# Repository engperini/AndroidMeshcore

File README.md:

# MeshCommunity

**English** · [Português](#português)

**One USB LoRa radio + your Android phone = a MeshCore node, a Meshtastic node or a raw LoRa terminal.
Switch networks with one tap. No firmware flashing, no Bluetooth, no second app.**

<p align="center">

  <br><sub>The same radio running <b>MeshCore</b>, <b>Meshtastic</b> and <b>generic LoRa</b>, one at a time.</sub>
</p>

> [!WARNING]
> Use at your own risk. You are responsible for transmitting only on frequencies and power levels that are legal
> where you are.

## Contents

- [What makes it different: the firmware runs on the phone](#what-makes-it-different-the-firmware-runs-on-the-phone)
- [Supported hardware](#supported-hardware)
- [Quick start](#quick-start)
- [Screens](#screens)
- [Features](#features)
- [Future: the radio without the cable](#future-the-radio-without-the-cable)
- [How it works inside](#how-it-works-inside)
- [Build](#build) · [Tests](#tests) · [Layout](#layout) · [Credits and license](#credits-and-license)

## What makes it different: the firmware runs on the phone

On a normal mesh radio, a microcontroller board runs the firmware and the phone is only a screen, connected over
Bluetooth. The network is decided by the firmware you flash: to go from MeshCore to Meshtastic you take a computer,
flash the board again, and switch to another app.

MeshCommunity turns that around. **The firmware runs inside the app, on the phone.** The USB radio is only a radio
(an SX1262 LoRa chip plus a tiny USB-to-SPI bridge), so it never needs to know which network you use.

```
  The usual way                                    MeshCommunity
  ─────────────                                    ─────────────
  📱 app ──Bluetooth──▶ 📟 board with MCU          📱 app + firmware (MeshCore, Meshtastic, LoRa)
                         └ runs ONE firmware          │
                           (reflash to change)        └──USB OTG──▶ 📻 radio only (no firmware)
```

What this gives you:

| | Usual mesh radio | MeshCommunity |
|---|---|---|
| Change network (MeshCore ↔ Meshtastic) | flash another firmware with a computer | **tap Settings → Mode** |
| Update the firmware | flash the board | **update the app** (APK) |
| Apps | one app per network | **one app** for all |
| Your data when you switch | lost when you reflash | **each mode keeps its own** identity, contacts, channels and messages |
| Radio hardware | board with a microcontroller | a **USB radio with no microcontroller** is enough |
| Link phone ↔ radio | Bluetooth (pairing, range) | **USB cable** (OTG) |
| Clock, GPS, battery | board's own | the **phone's** |

What to keep in mind:

- **One network at a time.** Switching takes a second, but the radio listens to one protocol at a time.
- **The node lives in the phone.** If you unplug the radio or the app is stopped, the node is offline: this is a
  companion for you to carry, not a standalone repeater on a rooftop.
- The radio draws its power from the phone (a few tens of mA receiving).

## Supported hardware

| Radio | What it is | Status |
|---|---|---|
| **USB MeshStick** (e.g. Elecrow MeshStick) | CH341A USB bridge (`1a86:5512`) + SX1262. Plug and play. | ✅ supported, field-tested |
| **Seeed XIAO nRF52840 + Wio-SX1262 kit** | The XIAO only works as a USB-to-SPI bridge, like the MeshStick's CH341: flash the [xiao-sx1262-usb-bridge](https://github.com/engperini/xiao-sx1262-usb-bridge) firmware **once** and never again. | ✅ supported, field-tested |
| **USB LoRa stick, no MCU** (CH341F + Wio-SX1262) | Our own 20.5 × 14 mm board, in [`hardware/`](hardware/), with JLCPCB order files and a 3D-printed case. | 🧪 v0.2 design, not built yet |

All of them run all three modes: the app drives every radio through the same USB driver. The XIAO kit is the
practical choice if you already have one; the MeshStick needs nothing at all.

<p align="center">
  <br>
  <sub>An Android phone + a USB MeshStick on an OTG adapter, receiving the MeshCore Brasil mesh.</sub>
</p>

You also need:

- An Android **8.0+** phone with **USB host/OTG** (almost every current phone).
- An **OTG** adapter or cable (e.g. USB-C → USB-A female).
- An **antenna** on the radio **before** you plug it in.

## Quick start

1. Download **`MeshCommunity.apk`** from [Releases](https://github.com/engperini/AndroidMeshcore/releases/latest) and
   install it (Android asks you to allow installs from unknown sources).
2. Attach the antenna, plug the radio into the phone with OTG, and allow **MeshCommunity to open** and to **access
   the USB device** (tick "always"). The app opens by itself next time you plug it in.
3. Choose the network in **Settings → Mode**, then:

**MeshCore**
- Settings → **LoRa radio**: pick your **region** (Brazil is preset: 923.125 MHz, 62.5 kHz, SF8, CR8), the **path
  bytes** (MeshCore Brasil: 2) and tap **Apply**. Under **Identity**, name your node.
- Menu ⋮ → **Send advert (flood)** so others find you, then say hi in the *Public* channel 👋

**Meshtastic**
- Settings → **Meshtastic radio**: choose the **region** (Meshtastic does not transmit until it is set; in Brazil
  most communities use **ANZ**, LongFast at 919.875 MHz) and keep the **LongFast** preset to talk to the default mesh.
- Under **Meshtastic node**, set your long and short name. Menu ⋮ → **Announce node** so others see you now.
- Chat in **#LongFast**, see who is around in **Nodes**, run a **Traceroute**, and find nodes on the **Map**.

**Generic LoRa**
- Settings → **Generic LoRa radio**: pick a preset or set frequency, bandwidth, SF, CR, sync word and power.
- The **LoRa** tab shows every packet heard on those parameters (text or hex, with RSSI/SNR) and sends your own:
  handy for your own sensors and telemetry.

To update, install the new APK over the old one: every mode keeps its data. Before changing phones, export your
MeshCore key in **Settings → Identity backup**.

> [!TIP]
> Some phones switch OTG off after a while or save battery aggressively. If the radio stops with the screen off,
> turn off battery optimisation for MeshCommunity.

## Screens

The screens are rendered by the app's tests (`ScreenshotTest`) with sample data, in English and Portuguese.

**MeshCore**

**Meshtastic**

**Generic LoRa**

## Features

The app is in **English and Portuguese** (it follows the phone; switch in **Settings → Language**). In every mode
the radio keeps running with the screen off, new messages raise a notification, and the app opens when you plug the
radio in.

### MeshCore mode

The [MeshCore](https://github.com/meshcore-dev/MeshCore) companion firmware (`MyMesh`), the same as on a MeshCore
radio, talking to the app with the official companion protocol.

- 💬 **Chats**: group channels and direct messages in one list, with unread counts.
  - **Channels**: *Public* comes preconfigured. Create a **#hashtag** channel (everyone using the same `#name` joins
    the same chat), a **new private** channel (random key) or join one **with a key**. Long-press → **QR code** to
    share. Your channel messages show **how many repeaters were heard repeating them** (tap to see which).
  - **Direct messages**: *sending → sent → delivered ✓✓* with the round-trip time; tap an unconfirmed one to resend.
  - **Rooms (room servers)**: log in from the chat; posts show their author.
- 👥 **Contacts**: search, filters, sorting and "last seen". Each contact shows its route, with **Discover route**,
  **Ping** for repeaters (SNR at each hop), **Use this route**, **Reset**, **QR code** and zero-hop share.
- 🛠️ **Remote admin** of repeaters, rooms and sensors: login, **status** (battery, uptime, queue, packets, airtime,
  RSSI/SNR, noise) and an encrypted **CLI terminal**. Every request shows *waiting → answered in N s* or *no answer*.
- 🔳 **`meshcore://` QR codes** and links, compatible with the official app.
- 🗺️ **Map** of contacts with GPS (OpenStreetMap, no API key).
- 📊 **Network**: node stats, SNR/RSSI chart, packets by type, **radio diagnostics** and the packet log.
- ⚙️ **Settings**: radio in 3 steps (**region → path bytes → power**, with an *Advanced* section), manual and
  automatic **adverts**, contact rules, telemetry sharing, location, and **identity backup** (export/restore the key).

### Meshtastic mode

The [Meshtastic firmware](https://github.com/meshtastic/firmware) itself (2.8), built for Android. It talks on the
air with any Meshtastic device: T-Beams, Heltecs, RAKs, other phones…

- 💬 **Chats**: the node's channels (the primary shows its preset name, e.g. *LongFast*) and direct messages. Your
  messages show when a node was heard passing them on (implicit ACK); direct ones turn *delivered ✓✓*.
- 📡 **Nodes**: every node heard, with hops, SNR, battery and last heard. **Traceroute** shows the path out and back
  with the SNR of each hop. Menu ⋮ → **Announce node** sends your NodeInfo now.
- 🗺️ **Map**: nodes that share a position. **Share my position** sends the phone's GPS as your node's position.
- ⚙️ **Settings**: long and short name, **region**, modem preset, hop limit, power, and **channels** (name and key,
  add or delete).
- The node uses the phone's clock and GPS, and runs in its own Android process.

### Generic LoRa mode

Raw LoRa packets with free parameters: frequency, bandwidth 7.8–500 kHz, SF5–12, CR 4/5–4/8, sync word, preamble and
power. Every packet heard shows up as **text or hex** with **RSSI/SNR** and a signal chart, and you can send your
own. Presets listen to the MeshCore and Meshtastic channels. Good for your own sensors, telemetry and experiments.

### MeshCore mode compared

| Feature | Official MeshCore app | MeshCoreRPI (Pi) | MeshCommunity |
|---|---|---|---|
| How it reaches the radio | BLE/USB to a node running firmware | SPI/USB on the Pi; clients over TCP | **USB OTG to the radio, the node runs on the phone** |
| Public, #hashtag and private channels | ✅ | via a client | ✅ |
| Direct messages with ACK and resend | ✅ | via a client | ✅ |
| Rooms (room servers) | ✅ | via a client | ✅ |
| Repeater admin (login, status, CLI) | ✅ | ✅ | ✅ |
| Discover / set route, ping with SNR per hop | ✅ | — | ✅ |
| `meshcore://` QR codes | ✅ | — | ✅ |
| Map | ✅ | ✅ (web) | ✅ |
| Stats, charts, packet log, radio diagnostics | partial | ✅ (web) | ✅ |
| Identity backup | ✅ | — | ✅ |
| Also runs Meshtastic and generic LoRa | — | — | ✅ |
| Sensor telemetry | ✅ | — | not yet |

## Future: the radio without the cable

Today the radio is plugged into the phone. These are the next ideas, keeping what makes MeshCommunity different:
**the protocols run in the app, and the radio never needs to be flashed to change networks.**

**1. A LoRa modem over Bluetooth or Wi-Fi.** Over USB the phone drives the radio chip command by command, which
needs the ~0.3 ms round trips of a cable. Without a cable the radio needs a small microcontroller that speaks in
whole packets: *"set 919.875 MHz, SF11"*, *"send these 40 bytes"*, *"received 52 bytes, RSSI −97"*. That is one
message per packet, fine over Bluetooth or Wi-Fi.

A modem is not the same as the official firmware, even on the same board:

| | Official firmware | LoRa modem |
|---|---|---|
| Knows | the whole protocol: routing, encryption, channels, nodes | only the radio: bytes in, bytes out |
| Networks | one, the one flashed | any; it doesn't know which |
| Change network or update the protocol | flash the board | tap in the app / update the app |
| Without the phone | keeps relaying and storing messages | does nothing |

So for one network and a wireless radio, the official firmware on a Bluetooth board is the simpler choice; the
modem is for using several networks, raw LoRa, or new protocols with one radio. The idea is proven: ham radio's KISS
TNCs (APRSdroid over Bluetooth) and Reticulum's [RNode](https://github.com/markqvist/RNode_Firmware) are LoRa
modems of this kind. Speaking the RNode protocol, if it fits, would let boards already flashed with RNode work here.

**2. The Raspberry Pi as the home radio.** Many of us already keep a Pi with an SX1262 and the antenna at the window,
running a MeshCore repeater (e.g. with [MeshCoreRPI](https://github.com/engperini/MeshCoreRPI)). The Pi would run a
small radio server, and the app would connect to it over the home Wi-Fi: from the sofa, switch the window antenna to
Meshtastic to see the community chat, use the generic LoRa terminal, or back to MeshCore. When the phone lets go,
the Pi goes back to being the repeater. (One radio listens on one frequency at a time: while you use Meshtastic,
the MeshCore repeater pauses.)

**3. MeshCore repeater and companion on the same radio.** The MeshCore companion firmware only lets a companion
repeat on 433.000, 869.000 and 918.000 MHz, so not on the Brazilian 923.125 MHz. That is a deliberate network rule.
Instead of bypassing it, the same radio can carry two nodes side by side: a real **repeater**, with its own identity
and announced as a repeater, and **your companion**. The Pi at the window, or the USB radio on the phone, serves
both.

## How it works inside

```
┌─────────────────────────── Android phone ───────────────────────────┐
│  MeshCommunity UI (Compose): chats, contacts/nodes, map, settings     │
│        │                                   │                          │
│  libmeshcore.so (NDK)                  :meshtastic process            │
│   ├ MeshCore companion firmware        libmeshtastic.so (NDK)         │
│   └ generic LoRa mode                   └ Meshtastic firmware 2.8      │
│        │                                   │                          │
│        └──────── USB radio driver (usbdevfs, no root) ────────┘        │
└──────────────────────────────────┬──────────────────────────────────┘
                                   │ USB OTG
        MeshStick (CH341 + SX1262) · XIAO + Wio-SX1262 bridge · USB LoRa stick
```

- **MeshCore** runs in `libmeshcore.so`, ported from [MeshCoreRPI](https://github.com/engperini/MeshCoreRPI).
  The generic LoRa mode lives in the same library.
- **Meshtastic** runs in `libmeshtastic.so`: the firmware's portduino/WASM build compiled for Android, in its own
  process, so a node restart is simply a fresh process.
- Both drive the SX1262 through the same USB code, over Android's USB host API (no root).
- Each protocol keeps its own data in the app: identities, nodes, channels, and the message history in SQLite.

## Build

Requirements: JDK 17, Android SDK (platform 35), NDK `27.2.12479018` and CMake `3.22.1`.

```bash
./gradlew assembleDebug        # app/build/outputs/apk/debug/app-debug.apk
./gradlew assembleRelease      # R8-minified APK
```

Every build, local or CI, is signed with the public test key in `app/meshcore-debug.jks`, so new APKs install over
the previous one and keep your data. It is public on purpose: anyone can build and contribute. A fork can use its own
key with `MESHCORE_KEYSTORE_FILE`, `MESHCORE_KEYSTORE_PASSWORD`, `MESHCORE_KEY_ALIAS` and `MESHCORE_KEY_PASSWORD`.

## Tests

- `tools/hosttest` builds a **MeshCore PC node** from the same sources as `libmeshcore.so`, with a UDP "radio".
  `TwoNodeMeshTest` runs two of them and drives them with the app's protocol code: adverts, direct messages with
  ACK, channels, routes, links, key backup and more.
- `tools/meshtastic/hosttest` builds the **Meshtastic engine on the PC** with the same sources and glue as the app
  (simulated radio) and drives it like the app does: config, rename, text, traceroute, region, position.
- `ScreenshotTest` / `ScreenshotTestEn` (Robolectric) render the screens above.

```bash
tools/hosttest/build.sh
tools/meshtastic/hosttest/build.sh
./gradlew testDebugUnitTest
```

GitHub Actions runs all of them and builds the APK on every push; a manual run with a version publishes the release.

## Layout

| Path | What it is |
|---|---|
| `app/src/main/cpp/meshcore/` | MeshCore core and companion firmware, ed25519 and Crypto, from MeshCoreRPI |
| `app/src/main/cpp/android/` | USB radio buses (`Ch341Bridge`, `XiaoBridge`), SX1262 driver, JNI of `libmeshcore.so` |
| `app/src/main/cpp/meshtastic/` | Meshtastic engine: firmware and libraries in `vendor/` (fetched by `tools/meshtastic/vendor.sh` at fixed revisions), Android glue in `android/` |
| `app/src/main/java/.../core/` | Controllers: `MeshController` (MeshCore), `MeshtasticController`, `LoraController` (modes, generic LoRa) |
| `app/src/main/java/.../mt/` | Meshtastic engine process (`MtEngineService`) |
| `app/src/main/java/.../service/` | Foreground service and USB (permission, wake lock, notifications) |
| `app/src/main/java/.../ui/` | Compose screens |
| `hardware/` | No-MCU USB LoRa stick (KiCad, JLCPCB files) and 3D-printed cases |
| `tools/` | PC test nodes for MeshCore and Meshtastic |

## Credits and license

- [MeshCore](https://github.com/meshcore-dev/MeshCore) by Scott Powell / rippleradios.com: MIT.
- [MeshCoreRPI](https://github.com/engperini/MeshCoreRPI): native Linux port, SX1262 and CH341 driver.
- [Meshtastic firmware](https://github.com/meshtastic/firmware) by the Meshtastic developers: **GPL-3.0**, with
  [RadioLib](https://github.com/jgromes/RadioLib) (MIT), [portduino](https://github.com/meshtastic/framework-portduino)
  (GPL-3.0), [nanopb](https://github.com/nanopb/nanopb) (zlib) and the other libraries listed in
  [`app/src/main/cpp/meshtastic/vendor/LICENSES.md`](app/src/main/cpp/meshtastic/vendor/LICENSES.md).
- [Arduino Crypto](https://github.com/rweather/arduinolibs) by Rhys Weatherley: MIT. ed25519 by Orson Peters: zlib.

This repository's own code is under the MIT license, see [LICENSE](LICENSE). The Meshtastic engine is GPL-3.0, so
the **APK, which includes it, is distributed under GPL-3.0**; its complete source is this repository.

If MeshCommunity is useful to you, a ⭐ on GitHub helps other people find it.

---

# Português

[English](#meshcommunity) · **Português**

**Um rádio LoRa USB + seu celular Android = um nó MeshCore, um nó Meshtastic ou um terminal LoRa.
Troque de rede com um toque. Sem gravar firmware, sem Bluetooth, sem segundo app.**

<p align="center">

  <br><sub>O mesmo rádio rodando <b>MeshCore</b>, <b>Meshtastic</b> e <b>LoRa genérico</b>, um de cada vez.</sub>
</p>

> [!WARNING]
> Use por sua conta e risco. Você é responsável por transmitir só em frequências e potências permitidas onde você
> está.

## Índice

- [O diferencial: o firmware roda no celular](#o-diferencial-o-firmware-roda-no-celular)
- [Hardware compatível](#hardware-compatível)
- [Começo rápido](#começo-rápido)
- [Telas](#telas)
- [Funcionalidades](#funcionalidades)
- [Futuro: o rádio sem o cabo](#futuro-o-rádio-sem-o-cabo)
- [Como funciona por dentro](#como-funciona-por-dentro)
- [Compilar](#compilar) · [Testes](#testes) · [Estrutura](#estrutura) · [Créditos e licença](#créditos-e-licença)

## O diferencial: o firmware roda no celular

Num rádio mesh comum, uma placa com microcontrolador roda o firmware e o celular é só a tela, ligado por Bluetooth.
Quem decide a rede é o firmware gravado: para trocar de MeshCore para Meshtastic, você pega um computador, grava a
placa de novo e troca de app.

O MeshCommunity inverte isso. **O firmware roda dentro do app, no celular.** O rádio USB é só rádio (um chip LoRa
SX1262 e uma pequena ponte USB→SPI), então ele nem precisa saber qual rede você usa.

```
  O jeito comum                                    MeshCommunity
  ─────────────                                    ─────────────
  📱 app ──Bluetooth──▶ 📟 placa com MCU           📱 app + firmware (MeshCore, Meshtastic, LoRa)
                         └ roda UM firmware           │
                           (regravar para trocar)     └──USB OTG──▶ 📻 só o rádio (sem firmware)
```

O que você ganha:

| | Rádio mesh comum | MeshCommunity |
|---|---|---|
| Trocar de rede (MeshCore ↔ Meshtastic) | gravar outro firmware com um computador | **tocar em Config → Modo** |
| Atualizar o firmware | gravar a placa | **atualizar o app** (APK) |
| Apps | um app para cada rede | **um app** para todas |
| Seus dados ao trocar | perdidos ao regravar | **cada modo guarda os seus**: identidade, contatos, canais e mensagens |
| Hardware do rádio | placa com microcontrolador | basta um **rádio USB sem microcontrolador** |
| Ligação celular ↔ rádio | Bluetooth (pareamento, alcance) | **cabo USB** (OTG) |
| Relógio, GPS, bateria | os da placa | os do **celular** |

O que é bom saber:

- **Uma rede por vez.** A troca leva um segundo, mas o rádio escuta um protocolo de cada vez.
- **O nó mora no celular.** Se você desplugar o rádio ou o app for encerrado, o nó fica fora do ar: é um companheiro
  para levar com você, não um repetidor autônomo no telhado.
- O rádio é alimentado pelo celular (algumas dezenas de mA recebendo).

## Hardware compatível

| Rádio | O que é | Status |
|---|---|---|
| **USB MeshStick** (ex.: Elecrow MeshStick) | Ponte USB CH341A (`1a86:5512`) + SX1262. Plugar e usar. | ✅ suportado, testado em campo |
| **Kit Seeed XIAO nRF52840 + Wio-SX1262** | O XIAO só faz a ponte USB→SPI, como o CH341 do MeshStick: grave o firmware [xiao-sx1262-usb-bridge](https://github.com/engperini/xiao-sx1262-usb-bridge) **uma vez** e nunca mais. | ✅ suportado, testado em campo |
| **Pendrive LoRa sem MCU** (CH341F + Wio-SX1262) | Nossa placa de 20,5 × 14 mm, em [`hardware/`](hardware/), com os arquivos para pedir na JLCPCB e caixinha para impressora 3D. | 🧪 projeto v0.2, ainda não fabricado |

Todos rodam os três modos: o app usa o mesmo driver USB para qualquer rádio. O kit XIAO é a escolha prática para quem
já tem um; o MeshStick não precisa de nada.

<p align="center">
  <br>
  <sub>Celular Android + USB MeshStick num adaptador OTG, recebendo a malha MeshCore Brasil.</sub>
</p>

Você também precisa de:

- Celular Android **8.0** ou mais novo com **USB Host/OTG** (quase todos os atuais).
- Adaptador ou cabo **OTG** (USB-C → USB-A fêmea, por exemplo).
- **Antena** conectada ao rádio **antes** de plugar.

## Começo rápido

1. Baixe o **`MeshCommunity.apk`** em [Releases](https://github.com/engperini/AndroidMeshcore/releases/latest) e
   instale (o Android pede para permitir a instalação de fontes desconhecidas).
2. Coloque a antena, plugue o rádio no celular pelo OTG e aceite **abrir o MeshCommunity** e **permitir o acesso ao
   dispositivo USB** (marque "usar sempre"). Da próxima vez, o app abre sozinho quando você plugar.
3. Escolha a rede em **Config → Modo** e então:

**MeshCore**
- Config → **Rádio LoRa**: escolha a **região** (o Brasil já vem pronto: 923,125 MHz, 62,5 kHz, SF8, CR8), os
  **bytes do caminho** (MeshCore Brasil: 2) e toque em **Aplicar**. Em **Identidade**, dê um nome ao seu nó.
- Menu ⋮ → **Enviar advert (flood)** para ser encontrado e dê um oi no canal *Public* 👋

**Meshtastic**
- Config → **Rádio Meshtastic**: escolha a **região** (o Meshtastic não transmite até ela ser definida; no Brasil a
  maioria das comunidades usa **ANZ**, LongFast em 919,875 MHz) e mantenha o preset **LongFast** para falar com a malha
  padrão.
- Em **Nó Meshtastic**, defina o nome longo e o curto. Menu ⋮ → **Anunciar nó** para aparecer para os outros na hora.
- Converse no **#LongFast**, veja quem está por perto em **Nós**, faça um **Traceroute** e encontre os nós no **Mapa**.

**LoRa genérico**
- Config → **Rádio LoRa genérico**: escolha uma predefinição ou ajuste frequência, largura de banda, SF, CR, sync word
  e potência.
- A aba **LoRa** mostra cada pacote ouvido com esses parâmetros (texto ou hex, com RSSI/SNR) e envia os seus: útil
  para seus sensores e telemetria.

Para atualizar, instale o APK novo por cima: todos os modos mantêm seus dados. Antes de trocar de celular, exporte sua
chave do MeshCore em **Config → Backup da identidade**.

> [!TIP]
> Alguns celulares desligam o OTG depois de um tempo ou economizam bateria de forma agressiva. Se o rádio parar com a
> tela apagada, desative a otimização de bateria para o MeshCommunity.

## Telas

As telas são geradas pelos testes do app (`ScreenshotTest`) com dados de exemplo, em português e inglês.

**MeshCore**

**Meshtastic**

**LoRa genérico**

## Funcionalidades

O app está em **português e inglês** (segue o idioma do celular; troque em **Config → Idioma**). Em todos os modos o
rádio continua ativo com a tela apagada, mensagens novas geram notificação e o app abre quando você pluga o rádio.

### Modo MeshCore

O firmware companion do [MeshCore](https://github.com/meshcore-dev/MeshCore) (`MyMesh`), o mesmo de um rádio
MeshCore, conversando com o app pelo protocolo companion oficial.

- 💬 **Conversas**: canais em grupo e mensagens diretas numa lista só, com não lidas.
  - **Canais**: o *Public* já vem configurado. Crie um canal **#hashtag** (todos que usam o mesmo `#nome` entram na
    mesma conversa), um canal **privado novo** (chave aleatória) ou entre num canal **com chave**. Toque e segure →
    **QR code** para compartilhar. Suas mensagens no canal mostram **quantas repetidoras foram ouvidas repassando**
    (toque para ver quais).
  - **Mensagens diretas**: *enviando → enviado → entregue ✓✓* com o tempo de ida e volta; toque numa sem
    confirmação para reenviar.
  - **Salas (room servers)**: login pelo próprio chat; as mensagens mostram o autor.
- 👥 **Contatos**: busca, filtros, ordenação e "visto há". Cada contato mostra a rota, com **Descobrir rota**,
  **Ping** para repetidores (SNR em cada salto), **Usar esta rota**, **Redefinir**, **QR code** e compartilhar
  zero-hop.
- 🛠️ **Administração remota** de repetidores, salas e sensores: login, **status** (bateria, uptime, fila, pacotes,
  tempo no ar, RSSI/SNR, ruído) e **terminal CLI** criptografado. Cada pedido mostra *aguardando → respondeu em N s*
  ou *sem resposta*.
- 🔳 **QR codes e links `meshcore://`**, compatíveis com o app oficial.
- 🗺️ **Mapa** dos contatos com GPS (OpenStreetMap, sem chave de API).
- 📊 **Rede**: estatísticas do nó, gráfico de SNR/RSSI, pacotes por tipo, **diagnóstico do rádio** e log de pacotes.
- ⚙️ **Config**: rádio em 3 passos (**região → bytes do caminho → potência**, com seção *Avançado*), **advert**
  manual e automático, regras de contatos, compartilhamento de telemetria, localização e **backup da identidade**
  (exportar/restaurar a chave).

### Modo Meshtastic

O próprio [firmware Meshtastic](https://github.com/meshtastic/firmware) (2.8), compilado para Android. Ele conversa
no ar com qualquer aparelho Meshtastic: T-Beam, Heltec, RAK, outros celulares…

- 💬 **Conversas**: os canais do nó (o primário mostra o nome do preset, ex.: *LongFast*) e mensagens diretas. Suas
  mensagens mostram quando um nó foi ouvido repassando (ACK implícito); as diretas ficam *entregue ✓✓*.
- 📡 **Nós**: todos os nós ouvidos, com saltos, SNR, bateria e quando foi ouvido. O **Traceroute** mostra o caminho de
  ida e volta com o SNR de cada salto. Menu ⋮ → **Anunciar nó** envia seu NodeInfo na hora.
- 🗺️ **Mapa**: os nós que compartilham posição. **Compartilhar posição** envia o GPS do celular como a posição do
  seu nó.
- ⚙️ **Config**: nome longo e curto, **região**, preset do modem, limite de saltos, potência e **canais** (nome e
  chave, adicionar ou excluir).
- O nó usa o relógio e o GPS do celular e roda num processo Android próprio.

### Modo LoRa genérico

Pacotes LoRa crus com parâmetros livres: frequência, largura de banda de 7,8 a 500 kHz, SF5–12, CR 4/5–4/8, sync word,
preâmbulo e potência. Cada pacote ouvido aparece em **texto ou hex** com **RSSI/SNR** e gráfico de sinal, e você pode
enviar os seus. Há predefinições para ouvir os canais MeshCore e Meshtastic. Bom para seus sensores, telemetria e
experiências.

### Comparação do modo MeshCore

| Funcionalidade | App oficial MeshCore | MeshCoreRPI (Pi) | MeshCommunity |
|---|---|---|---|
| Como chega ao rádio | BLE/USB com um nó que roda firmware | SPI/USB no Pi; clientes por TCP | **USB OTG no rádio, o nó roda no celular** |
| Canais Public, #hashtag e privados | ✅ | via cliente | ✅ |
| Mensagens diretas com ACK e reenvio | ✅ | via cliente | ✅ |
| Salas (room servers) | ✅ | via cliente | ✅ |
| Admin de repetidor (login, status, CLI) | ✅ | ✅ | ✅ |
| Descobrir/definir rota, ping com SNR por salto | ✅ | — | ✅ |
| QR codes `meshcore://` | ✅ | — | ✅ |
| Mapa | ✅ | ✅ (web) | ✅ |
| Estatísticas, gráficos, log de pacotes, diagnóstico do rádio | parcial | ✅ (web) | ✅ |
| Backup da identidade | ✅ | — | ✅ |
| Também roda Meshtastic e LoRa genérico | — | — | ✅ |
| Telemetria de sensores | ✅ | — | ainda não |

## Futuro: o rádio sem o cabo

Hoje o rádio fica plugado no celular. Estas são as próximas ideias, mantendo o que faz o MeshCommunity diferente:
**os protocolos rodam no app, e o rádio nunca precisa ser regravado para trocar de rede.**

**1. Um modem LoRa por Bluetooth ou Wi-Fi.** Pela USB, o celular controla o chip do rádio comando por comando, o que
exige as idas e voltas de ~0,3 ms de um cabo. Sem cabo, o rádio precisa de um pequeno microcontrolador que fala em
pacotes inteiros: *"ajuste 919,875 MHz, SF11"*, *"transmita estes 40 bytes"*, *"recebi 52 bytes, RSSI −97"*. É uma
mensagem por pacote, o que funciona bem por Bluetooth ou Wi-Fi.

Um modem não é o mesmo que o firmware oficial, mesmo na mesma placa:

| | Firmware oficial | Modem LoRa |
|---|---|---|
| Sabe | o protocolo inteiro: roteamento, criptografia, canais, nós | só o rádio: bytes entram, bytes saem |
| Redes | uma, a que foi gravada | qualquer uma; ele nem sabe qual |
| Trocar de rede ou atualizar o protocolo | regravar a placa | um toque no app / atualizar o app |
| Sem o celular | continua repetindo e guardando mensagens | não faz nada |

Por isso, para uma rede só com rádio sem fio, o firmware oficial numa placa com Bluetooth é a escolha mais simples; o
modem é para usar várias redes, LoRa livre ou protocolos novos com um rádio só. A ideia é comprovada: os TNC KISS do
radioamador (o APRSdroid usa por Bluetooth) e o [RNode](https://github.com/markqvist/RNode_Firmware) da rede
Reticulum são modems LoRa desse tipo. Falar o protocolo do RNode, se ele servir, permitiria usar aqui placas que já
têm o firmware RNode.

**2. O Raspberry Pi como o rádio de casa.** Muita gente já deixa um Pi com SX1262 e a antena na janela, rodando um
repetidor MeshCore (por exemplo com o [MeshCoreRPI](https://github.com/engperini/MeshCoreRPI)). O Pi rodaria um pequeno
servidor de rádio, e o app se conectaria a ele pelo Wi-Fi de casa: do sofá, você troca a antena da janela para o
Meshtastic e vê a conversa da comunidade, usa o terminal LoRa genérico ou volta para o MeshCore. Quando o celular
solta, o Pi volta a ser o repetidor. (Um rádio escuta uma frequência por vez: enquanto você usa o Meshtastic, o
repetidor MeshCore pausa.)

**3. Repetidor e companion MeshCore no mesmo rádio.** O firmware companion do MeshCore só deixa um companion repetir
em 433,000, 869,000 e 918,000 MHz, ou seja, não nos 923,125 MHz do Brasil. É uma regra intencional da rede. Em vez de
furá-la, o mesmo rádio pode carregar dois nós lado a lado: um **repetidor de verdade**, com identidade própria e
anunciado como repetidor, e o **seu companion**. O Pi na janela, ou o rádio USB no celular, atende os dois.

## Como funciona por dentro

```
┌────────────────────────── celular Android ──────────────────────────┐
│  Interface do MeshCommunity (Compose): conversas, contatos/nós, mapa  │
│        │                                   │                          │
│  libmeshcore.so (NDK)                  processo :meshtastic           │
│   ├ firmware companion MeshCore        libmeshtastic.so (NDK)         │
│   └ modo LoRa genérico                  └ firmware Meshtastic 2.8      │
│        │                                   │                          │
│        └────── driver USB do rádio (usbdevfs, sem root) ──────┘        │
└──────────────────────────────────┬──────────────────────────────────┘
                                   │ USB OTG
        MeshStick (CH341 + SX1262) · ponte XIAO + Wio-SX1262 · pendrive LoRa
```

- O **MeshCore** roda na `libmeshcore.so`, portada do [MeshCoreRPI](https://github.com/engperini/MeshCoreRPI). O modo
  LoRa genérico fica na mesma biblioteca.
- O **Meshtastic** roda na `libmeshtastic.so`: a versão portduino/WASM do firmware compilada para Android, num
  processo próprio, então reiniciar o nó é só iniciar um processo novo.
- Os dois controlam o SX1262 pelo mesmo código USB, pela API de USB host do Android (sem root).
- Cada protocolo guarda seus dados no app: identidades, nós, canais e o histórico de mensagens em SQLite.

## Compilar

Requisitos: JDK 17, Android SDK (platform 35), NDK `27.2.12479018` e CMake `3.22.1`.

```bash
./gradlew assembleDebug        # app/build/outputs/apk/debug/app-debug.apk
./gradlew assembleRelease      # APK com R8
```

Todo build, local ou no CI, é assinado com a chave pública de teste em `app/meshcore-debug.jks`, então os APKs novos
instalam por cima e mantêm seus dados. Ela é pública de propósito, para qualquer pessoa compilar e contribuir. Um fork
pode usar a própria chave com `MESHCORE_KEYSTORE_FILE`, `MESHCORE_KEYSTORE_PASSWORD`, `MESHCORE_KEY_ALIAS` e
`MESHCORE_KEY_PASSWORD`.

## Testes

- `tools/hosttest` gera um **nó MeshCore para PC** com as mesmas fontes da `libmeshcore.so`, com um "rádio" UDP. O
  `TwoNodeMeshTest` roda dois deles e os controla com o código de protocolo do app: adverts, mensagens diretas com
  ACK, canais, rotas, links, backup da chave e mais.
- `tools/meshtastic/hosttest` gera o **motor Meshtastic no PC** com as mesmas fontes e cola do app (rádio simulado) e
  o controla como o app: configuração, nome, texto, traceroute, região e posição.
- `ScreenshotTest` / `ScreenshotTestEn` (Robolectric) geram as telas acima.

```bash
tools/hosttest/build.sh
tools/meshtastic/hosttest/build.sh
./gradlew testDebugUnitTest
```

O GitHub Actions roda todos eles e gera o APK a cada push; uma execução manual com a versão publica a release.

## Estrutura

| Caminho | O que é |
|---|---|
| `app/src/main/cpp/meshcore/` | Núcleo e firmware companion do MeshCore, ed25519 e Crypto, do MeshCoreRPI |
| `app/src/main/cpp/android/` | Barramentos USB do rádio (`Ch341Bridge`, `XiaoBridge`), driver SX1262, JNI da `libmeshcore.so` |
| `app/src/main/cpp/meshtastic/` | Motor Meshtastic: firmware e bibliotecas em `vendor/` (baixados por `tools/meshtastic/vendor.sh` em revisões fixas), cola Android em `android/` |
| `app/src/main/java/.../core/` | Controladores: `MeshController` (MeshCore), `MeshtasticController`, `LoraController` (modos, LoRa genérico) |
| `app/src/main/java/.../mt/` | Processo do motor Meshtastic (`MtEngineService`) |
| `app/src/main/java/.../service/` | Serviço em primeiro plano e USB (permissão, wake lock, notificações) |
| `app/src/main/java/.../ui/` | Telas Compose |
| `hardware/` | Pendrive LoRa USB sem MCU (KiCad, arquivos JLCPCB) e caixinhas para impressão 3D |
| `tools/` | Nós de teste para PC, MeshCore e Meshtastic |

## Créditos e licença

- [MeshCore](https://github.com/meshcore-dev/MeshCore), de Scott Powell / rippleradios.com: MIT.
- [MeshCoreRPI](https://github.com/engperini/MeshCoreRPI): port nativo para Linux, driver SX1262 e CH341.
- [Firmware Meshtastic](https://github.com/meshtastic/firmware), dos desenvolvedores do Meshtastic: **GPL-3.0**, com
  [RadioLib](https://github.com/jgromes/RadioLib) (MIT), [portduino](https://github.com/meshtastic/framework-portduino)
  (GPL-3.0), [nanopb](https://github.com/nanopb/nanopb) (zlib) e as outras bibliotecas listadas em
  [`app/src/main/cpp/meshtastic/vendor/LICENSES.md`](app/src/main/cpp/meshtastic/vendor/LICENSES.md).
- [Arduino Crypto](https://github.com/rweather/arduinolibs), de Rhys Weatherley: MIT. ed25519, de Orson Peters: zlib.

O código próprio deste repositório está sob a licença MIT, veja [LICENSE](LICENSE). O motor Meshtastic é GPL-3.0, por
isso o **APK, que o inclui, é distribuído sob a GPL-3.0**; o código-fonte completo é este repositório.

Se o MeshCommunity for útil para você, uma ⭐ no GitHub ajuda outras pessoas a encontrá-lo.

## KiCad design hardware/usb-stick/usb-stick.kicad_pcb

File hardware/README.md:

# Hardware

**English** · [Português](#português)

Two ways to give the phone a LoRa radio over USB, both running the MeshCore node **on the phone**:

| | USB LoRa stick (this folder) | XIAO kit |
|---|---|---|
| Inside | CH341F + Seeed Wio-SX1262 module | Seeed XIAO nRF52840 + Wio-SX1262 |
| Microcontroller | **none** | nRF52840, as a USB-SPI bridge |
| Firmware to flash | **none** | [xiao-sx1262-usb-bridge](https://github.com/engperini/xiao-sx1262-usb-bridge) |
| Works with | this app | this app (bridge firmware) or the official MeshCore app (MeshCore firmware) |
| Size | board 20.5 × 14 mm | 21 × 17.8 mm stack |
| Status | **v0.2 design, not built yet** | tested |

Both use the same case design: a straight USB-C male-male adapter inside a small 3D-printed box.

## USB LoRa stick (`usb-stick/`)

Same wiring as the USB MeshStick, so the app's CH341 driver works unchanged:

| CH341F | SX1262 module |
|---|---|
| D0 | NSS |
| D2 | RESET |
| D4 | BUSY |
| D6 | DIO1 |
| D3 / D5 / D7 | SCK / MOSI / MISO |
| D1 | RF_SW (high = receive) |

- The **Wio-SX1262** is the same radio as in the XIAO kit: 11.6 × 11 mm, TCXO on DIO3, DIO2 switches it to
  transmit internally, IPEX for the antenna. Its RF_SW pin selects receive; the app drives it from CH341 D1,
  the pin the MeshStick leaves free for RXEN (on a MeshStick D1 is unconnected, so nothing changes there).
- The CH341F runs on its **internal clock** (no crystal) and starts in SPI mode, `1a86:5512`,
  because SDA is tied low.
- 3.3 V from an ME6211 LDO (500 mA).
- Green LED: on when the phone has configured the stick.
- Board: 20.5 × 14 mm, 2 layers, 1.6 mm. Everything is on top except the radio module, which is
  **hand-soldered on the back** (12 edge pads, 1.27 mm pitch). The antenna plugs into the module's IPEX.

### Ordering at JLCPCB

1. **PCB:** upload `usb-stick/fab/usb-stick-gerbers.zip` (2 layers, 1.6 mm, any colour).
2. **Assembly (top side):** upload `usb-stick-bom.csv` and `usb-stick-cpl.csv`. In the placement preview,
   check the rotation of U1 (pin 1 dot), U2, U3, D1 and J1, and fix any that JLCPCB shows turned.
3. **By hand:** buy the Seeed **Wio-SX1262** module (the HF one, 862–930 MHz, with IPEX) and solder it on the
   back: pin 1 (RF_SW) at the mark, IPEX towards the far end (the silkscreen shows both). A fine tip and flux
   are enough for the 1.27 mm edge pads.
4. Connect the antenna, plug the stick into the phone through the straight USB-C male-male adapter, open the
   app.

### Rebuilding

The board is generated from code: `gen_board.py` (parts and netlist), `route.py` (a small two-layer
negotiated router), `drc.py` (KiCad DRC) and `fab.py` (JLCPCB files). `build.sh` runs them all. You can also
open `usb-stick.kicad_pcb` in KiCad 7+ and edit it by hand.

### Known limits of v0.1

- It uses a **female** USB-C socket plus the adapter, because JLCPCB's parts library has no board-mount
  male plug. A male plug would make it shorter.
- The Wio-SX1262 is not in JLCPCB's library, so it is soldered by hand.
- The land pattern comes from Seeed's own footprint file; check pin 1 and the IPEX corner against the module.
- Needs the app version that drives D1 as RXEN (after v0.2.0).
- Not built or tested yet. Treat v0.2 as a prototype. (v0.1, with a Waveshare Core1262-HF, is in the git
  history.)

## Cases (`cases/`)

OpenSCAD sources with the measurements at the top, and ready STL files:

| File | For |
|---|---|
| `case_stick_base.stl`, `case_stick_lid.stl` | the USB LoRa stick |
| `case_xiao_base.stl`, `case_xiao_lid.stl` | the XIAO nRF52840 + Wio-SX1262 kit |

- Import the STL files in Bambu Studio (or any slicer). PLA or PETG, 0.2 mm layers, no supports: print the
  base open side up and the lid flat side down.
- **Measure your adapter and boards first.** Straight USB-C adapters vary; the defaults are typical sizes.
  Change the numbers at the top of `case_*.scad`, then export again in OpenSCAD (F6, then *Export as STL*), or
  run `openscad -o case_stick_base.stl -D 'part="base"' case_stick.scad`.
- The adapter sits behind a thin front lip, so it does not come out when you unplug from the phone. The lid
  is a press fit (`fit` in `case_lib.scad`). The rear slot is for the antenna cable.

---

## Português

Duas formas de dar ao celular um rádio LoRa pela USB, as duas com o nó MeshCore rodando **no celular**:

| | Pendrive LoRa (esta pasta) | Kit XIAO |
|---|---|---|
| Dentro | CH341F + módulo Seeed Wio-SX1262 | Seeed XIAO nRF52840 + Wio-SX1262 |
| Microcontrolador | **nenhum** | nRF52840, como ponte USB-SPI |
| Firmware para gravar | **nenhum** | [xiao-sx1262-usb-bridge](https://github.com/engperini/xiao-sx1262-usb-bridge) |
| Funciona com | este app | este app (firmware da ponte) ou o app oficial do MeshCore (firmware MeshCore) |
| Tamanho | placa de 20,5 × 14 mm | conjunto de 21 × 17,8 mm |
| Situação | **projeto v0.2, ainda não fabricado** | testado |

As duas usam a mesma ideia de caixinha: um adaptador USB-C macho-macho reto dentro de uma caixa impressa em 3D.

## Pendrive LoRa (`usb-stick/`)

Mesma ligação do USB MeshStick, então o driver do CH341 no app funciona sem mudança:

| CH341F | Módulo SX1262 |
|---|---|
| D0 | NSS |
| D2 | RESET |
| D4 | BUSY |
| D6 | DIO1 |
| D3 / D5 / D7 | SCK / MOSI / MISO |
| D1 | RF_SW (nível alto = recepção) |

- O **Wio-SX1262** é o mesmo rádio do kit XIAO: 11,6 × 11 mm, TCXO no DIO3, DIO2 chaveando a transmissão por
  dentro e IPEX para a antena. O pino RF_SW seleciona a recepção; o app aciona ele pelo D1 do CH341, o pino que
  o MeshStick deixa livre para RXEN (no MeshStick o D1 não está ligado, então nada muda lá).
- O CH341F usa o **clock interno** (sem cristal) e liga no modo SPI, `1a86:5512`, porque o SDA está no GND.
- 3,3 V de um regulador ME6211 (500 mA).
- LED verde: acende quando o celular reconhece o pendrive.
- Placa: 20,5 × 14 mm, 2 camadas, 1,6 mm. Tudo fica em cima, menos o módulo de rádio, que é **soldado à mão
  embaixo** (12 pads na borda, passo de 1,27 mm). A antena encaixa no IPEX do módulo.

### Como encomendar na JLCPCB

1. **Placa:** envie `usb-stick/fab/usb-stick-gerbers.zip` (2 camadas, 1,6 mm, qualquer cor).
2. **Montagem (lado de cima):** envie `usb-stick-bom.csv` e `usb-stick-cpl.csv`. Na prévia da montagem,
   confira a rotação de U1 (bolinha do pino 1), U2, U3, D1 e J1 e corrija o que aparecer girado.
3. **À mão:** compre o módulo Seeed **Wio-SX1262** (o HF, 862–930 MHz, com IPEX) e solde embaixo: pino 1
   (RF_SW) na marca e IPEX virado para a ponta oposta ao USB (a serigrafia mostra os dois). Ponta fina e fluxo
   bastam para os pads de 1,27 mm.
4. Ligue a antena, conecte o pendrive ao celular pelo adaptador USB-C macho-macho reto e abra o app.

### Como refazer

A placa é gerada por código: `gen_board.py` (componentes e ligações), `route.py` (um roteador negociado de
duas camadas), `drc.py` (DRC do KiCad) e `fab.py` (arquivos da JLCPCB). O `build.sh` roda tudo. Também dá
para abrir o `usb-stick.kicad_pcb` no KiCad 7+ e editar à mão.

### Limites conhecidos da v0.1

- Usa conector USB-C **fêmea** mais o adaptador, porque a biblioteca de peças da JLCPCB não tem plugue macho
  de placa. Um plugue macho deixaria mais curto.
- O Wio-SX1262 não está na biblioteca da JLCPCB, então é soldado à mão.
- O desenho dos pads vem do arquivo de footprint da própria Seeed; confira o pino 1 e o canto do IPEX no módulo.
- Precisa da versão do app que aciona o D1 como RXEN (depois da v0.2.0).
- Ainda não foi fabricado nem testado. Trate a v0.2 como protótipo. (A v0.1, com o Waveshare Core1262-HF, fica
  no histórico do git.)

## Caixinhas (`cases/`)

Fontes em OpenSCAD com as medidas no topo, e arquivos STL prontos:

| Arquivo | Para |
|---|---|
| `case_stick_base.stl`, `case_stick_lid.stl` | o pendrive LoRa |
| `case_xiao_base.stl`, `case_xiao_lid.stl` | o kit XIAO nRF52840 + Wio-SX1262 |

- Importe os STL no Bambu Studio (ou outro fatiador). PLA ou PETG, camadas de 0,2 mm, sem suporte: a base
  com a abertura para cima e a tampa com o lado liso para baixo.
- **Meça antes o seu adaptador e as placas.** Os adaptadores USB-C retos variam; os valores padrão são
  típicos. Ajuste os números no topo do `case_*.scad` e exporte de novo no OpenSCAD (F6, depois *Export as
  STL*), ou rode `openscad -o case_stick_base.stl -D 'part="base"' case_stick.scad`.
- O adaptador fica atrás de um lábio fino na frente, para não sair quando você puxa do celular. A tampa
  encaixa por pressão (`fit` em `case_lib.scad`). O rasgo de trás é para o cabo da antena.

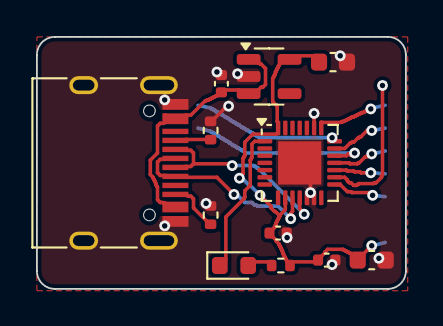
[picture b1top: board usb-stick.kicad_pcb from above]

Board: 2 copper layers, 20.5 x 14.0 mm, 13 parts (1 on the bottom side), 17 nets.

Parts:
C1: 1uF; C_0402_1005Metric
C2, C5: 10uF; C_0603_1608Metric
C3, C6: 100nF; C_0402_1005Metric
D1: Green; LED_0603_1608Metric
J1: USB-C 16P; USB_C_Receptacle_HRO_TYPE-C-31-M-12
M1: Wio-SX1262; Seeed_Wio-SX1262_MODULE12P-1.27-11x11.6mm
R1, R2: 5.1k; R_0402_1005Metric
R5: 1k; R_0402_1005Metric
U1: CH341F; QFN-28-1EP_4x4mm_P0.4mm_EP2.4x2.4mm
U2: ME6211C33M5G-N; SOT-23-5

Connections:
+3V3: C2.1, C3.1, C5.1, C6.1, M1.8, R5.2, U1.9, U1.28, U2.5
ACT_N: D1.1, U1.1
CC1: J1.A5, R1.1
CC2: J1.B5, R2.1
GND: C1.2, C2.2, C3.2, C5.2, C6.2, J1.A1, J1.A12, J1.B1, J1.B12, J1.S1, M1.7, M1.10, R1.2, R2.2, U1.12, U1.13, U1.23, U1.29, U2.2
LED_A: D1.2, R5.1
LORA_BUSY: M1.11, U1.19
LORA_DIO1: M1.12, U1.21
LORA_MISO: M1.2, U1.22
LORA_MOSI: M1.3, U1.20
LORA_NSS: M1.6, U1.15
LORA_RESET: M1.5, U1.17
LORA_RXEN: M1.1, U1.16
LORA_SCK: M1.4, U1.18
USB_DN: J1.A7, J1.B7, U1.11
USB_DP: J1.A6, J1.B6, U1.10
VBUS: C1.1, J1.A4, J1.A9, J1.B4, J1.B9, U2.1, U2.3

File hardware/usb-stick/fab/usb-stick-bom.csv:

Comment,Designator,Footprint,LCSC Part #
1uF,C1,C_0402_1005Metric,C52923
10uF,"C2,C5",C_0603_1608Metric,C19702
100nF,"C3,C6",C_0402_1005Metric,C1525
Green,D1,LED_0603_1608Metric,C72043
USB-C 16P,J1,USB_C_Receptacle_HRO_TYPE-C-31-M-12,C165948
5.1k,"R1,R2",R_0402_1005Metric,C25905
1k,R5,R_0402_1005Metric,C11702
CH341F,U1,QFN-28-1EP_4x4mm_P0.4mm_EP2.4x2.4mm,C412870
ME6211C33M5G-N,U2,SOT-23-5,C82942

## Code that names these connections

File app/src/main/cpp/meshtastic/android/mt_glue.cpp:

// Android glue for the Meshtastic firmware, adapted from its WASM glue
// (src/platform/portduino/wasm/portduino_glue_wasm.cpp, GPL-3.0, the Meshtastic authors).
//
// It supplies what the firmware's WASM build expects from its host: the LoRa adapter config
// (wasm_config_apply), the data directory, the node's MAC (its identity), the PhoneAPI seam the app
// talks to (ToRadio / FromRadio protobufs), and the framework symbols the excluded Linux core would
// provide (delay, random, reboot...). Everything runs on the radio thread (mt_jni.cpp).

#include "mt_glue.h"

#include "MeshRadio.h"
#include "MeshService.h"
#include "NodeDB.h"
#include "PhoneAPI.h"
#include "PortduinoFS.h"
#include "PortduinoGlue.h"
#include "RadioInterface.h"
#include "gps/RTC.h"

#include <atomic>
#include <chrono>
#include <condition_variable>
#include <mutex>
#include <cstdio>
#include <cstdlib>
#include <cstring>
#include <fcntl.h>
#include <string>
#include <sys/stat.h>
#include <unistd.h>

namespace {
std::string g_root = "/tmp/meshtastic";
std::atomic<bool> g_reboot{false};
}

extern "C" volatile bool g_wasm_in_firmware = false;

void mt_set_data_root(const std::string& root)
{
    g_root = root;
}

bool mt_take_reboot_request()
{
    return g_reboot.exchange(false);
}

void wasm_fs_sync() {}   // files are written straight to the app's storage

void mt_fs_mount()
{
    mkdir(g_root.c_str(), 0700);
    mkdir((g_root + "/prefs").c_str(), 0700);
    mkdir((g_root + "/oem").c_str(), 0700);
    portduinoVFS->mountpoint(g_root.c_str());
}

// The node's MAC: its lower 4 bytes become the NodeNum, the node's identity on the mesh. Generated
// once (locally administered, unicast) and kept with the node's data.
static std::string resolveMac()
{
    const std::string path = g_root + "/oem/mac";
    if (FILE* f = fopen(path.c_str(), "rb")) {
        char buf[13] = {0};
        const size_t n = fread(buf, 1, 12, f);
        fclose(f);
        if (n == 12) return std::string(buf, 12);
    }
    unsigned char m[6] = {0};
    const int fd = open("/dev/urandom", O_RDONLY);
    if (fd >= 0) {
        if (read(fd, m, sizeof(m)) != static_cast<ssize_t>(sizeof(m))) {
            for (auto& b : m) b = static_cast<unsigned char>(rand());
        }
        close(fd);
    }
    m[0] = (m[0] | 0x02) & 0xFE;
    char hex[13];
    snprintf(hex, sizeof(hex), "%02X%02X%02X%02X%02X%02X", m[0], m[1], m[2], m[3], m[4], m[5]);
    if (FILE* f = fopen(path.c_str(), "wb")) {
        fwrite(hex, 1, 12, f);
        fclose(f);
    }
    return std::string(hex, 12);
}

// LoRa adapter: an SX1262 behind a CH341 (MeshStick, USB LoRa stick) or the XIAO bridge, both addressed
// with the MeshStick's D-lines (pinedio_bus.cpp maps them for the XIAO): CS D0, RESET D2, BUSY D4,
// IRQ D6, RXEN D1, 1.8 V TCXO on DIO3, DIO2 as RF switch. Called from portduinoSetup().
void wasm_config_apply()
{
    auto setPin = [](pinMapping& p, int n) {
        p.pin = n;
        p.enabled = true;
    };
    if (mt_use_simradio()) {
        portduino_config.lora_module = use_simradio;
    } else {
        portduino_config.lora_module = use_sx1262;
        portduino_config.lora_usb_vid = 0x1A86;
        portduino_config.lora_usb_pid = 0x5512;
        portduino_config.lora_usb_serial_num = "";
        portduino_config.dio2_as_rf_switch = true;
        portduino_config.dio3_tcxo_voltage = 1800;
        portduino_config.spiSpeed = 2000000;
        setPin(portduino_config.lora_cs_pin, 0);
        setPin(portduino_config.lora_irq_pin, 6);
        setPin(portduino_config.lora_busy_pin, 4);
        setPin(portduino_config.lora_reset_pin, 2);
        setPin(portduino_config.lora_rxen_pin, 1);
    }
    portduino_config.lora_spi_dev = "ch341";
    portduino_config.displayPanel = no_screen;
    portduino_config.has_gps = false;
    portduino_config.MaxNodes = 200;
    portduino_config.mac_address = resolveMac();
}

// Region from the app (same path as the WASM build's wasm_set_region / AdminModule). 0 ok, -1 invalid.
int mt_set_region(int region)
{
    auto newRegion = static_cast<meshtastic_Config_LoRaConfig_RegionCode>(region);
    if (config.lora.region == newRegion) return 0;
    meshtastic_Config_LoRaConfig validated = config.lora;
    validated.region = newRegion;
    if (!(RadioInterface::validateConfigRegion(validated) && RadioInterface::validateConfigLora(validated))) return -1;
    int changes = SEGMENT_CONFIG;
    const bool wasUnset = config.lora.region == meshtastic_Config_LoRaConfig_RegionCode_UNSET;
    if (wasUnset && newRegion > meshtastic_Config_LoRaConfig_RegionCode_UNSET) {
#if !(MESHTASTIC_EXCLUDE_PKI_KEYGEN || MESHTASTIC_EXCLUDE_PKI)
        if (nodeDB && nodeDB->ensurePkiIdentity()) changes |= SEGMENT_DEVICESTATE | SEGMENT_NODEDATABASE;
#endif
        validated.tx_enabled = true;
    }
    if (!wasUnset && newRegion == meshtastic_Config_LoRaConfig_RegionCode_UNSET) validated.tx_enabled = false;
    config.lora = validated;
    initRegion();
    if (service) service->reloadConfig(changes);
    return 0;
}

void mt_sync_clock()
{
    struct timeval tv;
    if (gettimeofday(&tv, nullptr) == 0 && tv.tv_sec > 1700000000) perhapsSetRTC(RTCQualityNTP, &tv);
}

// ---- PhoneAPI: the app is always the connected client
class AppPhoneAPI : public PhoneAPI
{
  public:
    bool checkIsConnected() override { return true; }
};

static AppPhoneAPI* g_phone = nullptr;

static AppPhoneAPI* phone()
{
    if (!g_phone && service) g_phone = new AppPhoneAPI();
    return g_phone;
}

bool mt_api_to_radio(const uint8_t* buf, size_t len)
{
    AppPhoneAPI* p = phone();
    return p && p->handleToRadio(const_cast<uint8_t*>(buf), len);
}

size_t mt_api_from_radio(uint8_t* out, size_t max)
{
    AppPhoneAPI* p = phone();
    if (!p || max < 512 || !p->available()) return 0;
    return p->getFromRadio(out);
}

// ---- idle wait of the firmware loop
namespace {
std::mutex g_idle_mutex;
std::condition_variable g_idle_cv;
bool g_wake_flag = false;
constexpr auto IRQ_POLL = std::chrono::milliseconds(4);
}

void mt_wake()
{
    {
        std::lock_guard<std::mutex> lock(g_idle_mutex);
        g_wake_flag = true;
    }
    g_idle_cv.notify_all();
}

void mt_idle(unsigned int ms)
{
    const auto end = std::chrono::steady_clock::now() + std::chrono::milliseconds(ms);
    for (;;) {
        if (mt_poll_irqs()) return;
        std::unique_lock<std::mutex> lock(g_idle_mutex);
        const auto now = std::chrono::steady_clock::now();
        if (g_wake_flag || now >= end) {
            g_wake_flag = false;
            return;
        }
        g_idle_cv.wait_until(lock, std::min(end, now + IRQ_POLL), [] { return g_wake_flag; });
    }
}

// ---- framework symbols the excluded linux/LinuxCommon.cpp would provide
void delay(unsigned long ms)
{
    usleep(ms * 1000);
}
void yield(void)
{
    usleep(0);
}
long random(long howbig)
{
    return howbig > 0 ? (::rand() % howbig) : 0;
}
long random(long howsmall, long howbig)
{
    return howsmall >= howbig ? howsmall : howsmall + random(howbig - howsmall);
}
void randomSeed(unsigned long seed)
{
    ::srand(static_cast<unsigned>(seed));
}
// The node cannot restart its process; the app restarts the radio thread instead.
void reboot()
{
    g_reboot.store(true);
}
void tone(unsigned char, unsigned int, unsigned long) {}
void noTone(unsigned char) {}
void delayMicroseconds(unsigned int us)
{
    usleep(us);
}
bool shouldWakeOnReceivedMessage()
{
    return false;
}
void initApiServer(int) {}
void deInitApiServer() {}

// Referenced by modules that are built even with the input broker excluded; there is none on a phone.
class InputBroker;
InputBroker* inputBroker = nullptr;
// The GPS code checks for these input devices (built with the input broker); a phone has none.
class UpDownInterruptImpl1;
UpDownInterruptImpl1* upDownInterruptImpl1 = nullptr;
class RotaryEncoderInterruptImpl1;
RotaryEncoderInterruptImpl1* rotaryEncoderInterruptImpl1 = nullptr;

// Command-line arguments come from the framework's main(), which the app does not use.
#include <argp.h>
void portduinoAddArguments(const struct argp_child&, void*) {}
